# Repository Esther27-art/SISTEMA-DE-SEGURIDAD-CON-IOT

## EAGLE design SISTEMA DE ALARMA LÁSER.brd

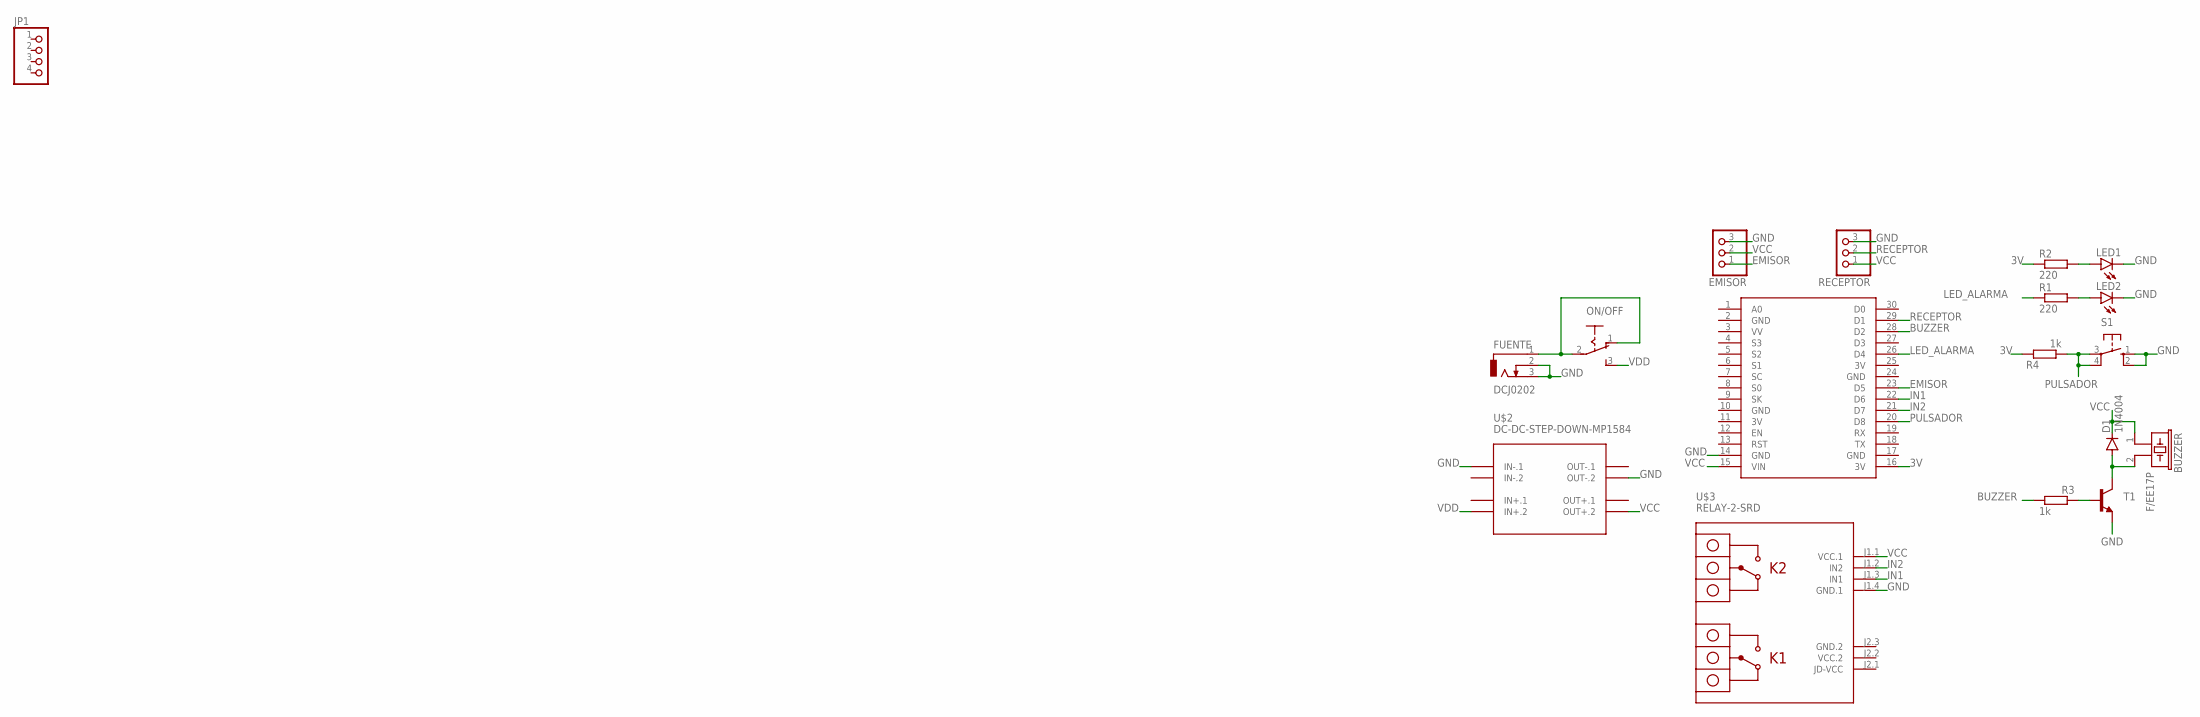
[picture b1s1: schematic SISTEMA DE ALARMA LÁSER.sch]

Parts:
BUZZER: F/EE17P
D1: 1N4004; DO41-10
EMISOR: PINHD-1X3; 1X03
FUENTE: DCJ0202
JP1: PINHD-1X4; 1X04
LED1, LED2: LED5MM
ON/OFF: 255SB
R1, R2: 220; 0204/7
R3, R4: 1k; 0204/7
RECEPTOR: PINHD-1X3; 1X03
S1: 10-XX; B3F-10XX
T1: 2N2222-NPN-TO92-EBC; TO92-EBC
U$1: NODEMCU
U$2: DC-DC-STEP-DOWN-MP1584
U$3: RELAY-2-SRD

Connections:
3V: R2.1, R4.2, U$1.11 (3V), U$1.16 (3V), U$1.25 (3V)
BUZZER: R3.1, U$1.28 (D2)
EMISOR: EMISOR.1, U$1.23 (D5)
GND: EMISOR.3, FUENTE.2, FUENTE.3, LED1.K (C), LED2.K (C), RECEPTOR.3, S1.1 (S), S1.2 (S1), T1.E, U$1.2 (GND), U$1.10 (GND), U$1.14 (GND), U$1.17 (GND), U$1.24 (GND), U$2.IN-.1, U$2.OUT-.2, U$3.J1.4 (GND.1)
GND.2: U$3.J2.3 (GND.2)
IN1: U$1.22 (D6), U$3.J1.3 (IN1)
IN2: U$1.21 (D7), U$3.J1.2 (IN2)
LED_ALARMA: R1.1, U$1.26 (D4)
unnamed: LED1.A, R2.2
unnamed: LED2.A, R1.2
unnamed: R3.2, T1.B
unnamed: BUZZER.2, D1.A, T1.C
unnamed: FUENTE.1, ON/OFF.1 (O), ON/OFF.2
PULSADOR: R4.1, S1.3, S1.4 (P1), U$1.20 (D8)
RECEPTOR: RECEPTOR.2, U$1.29 (D1)
VCC: BUZZER.1, D1.C, EMISOR.2, RECEPTOR.1, U$1.15 (VIN), U$2.OUT+.2, U$3.J1.1 (VCC.1)
VCC.2: U$3.J2.2 (VCC.2)
VDD: ON/OFF.3 (S), U$2.IN+.2

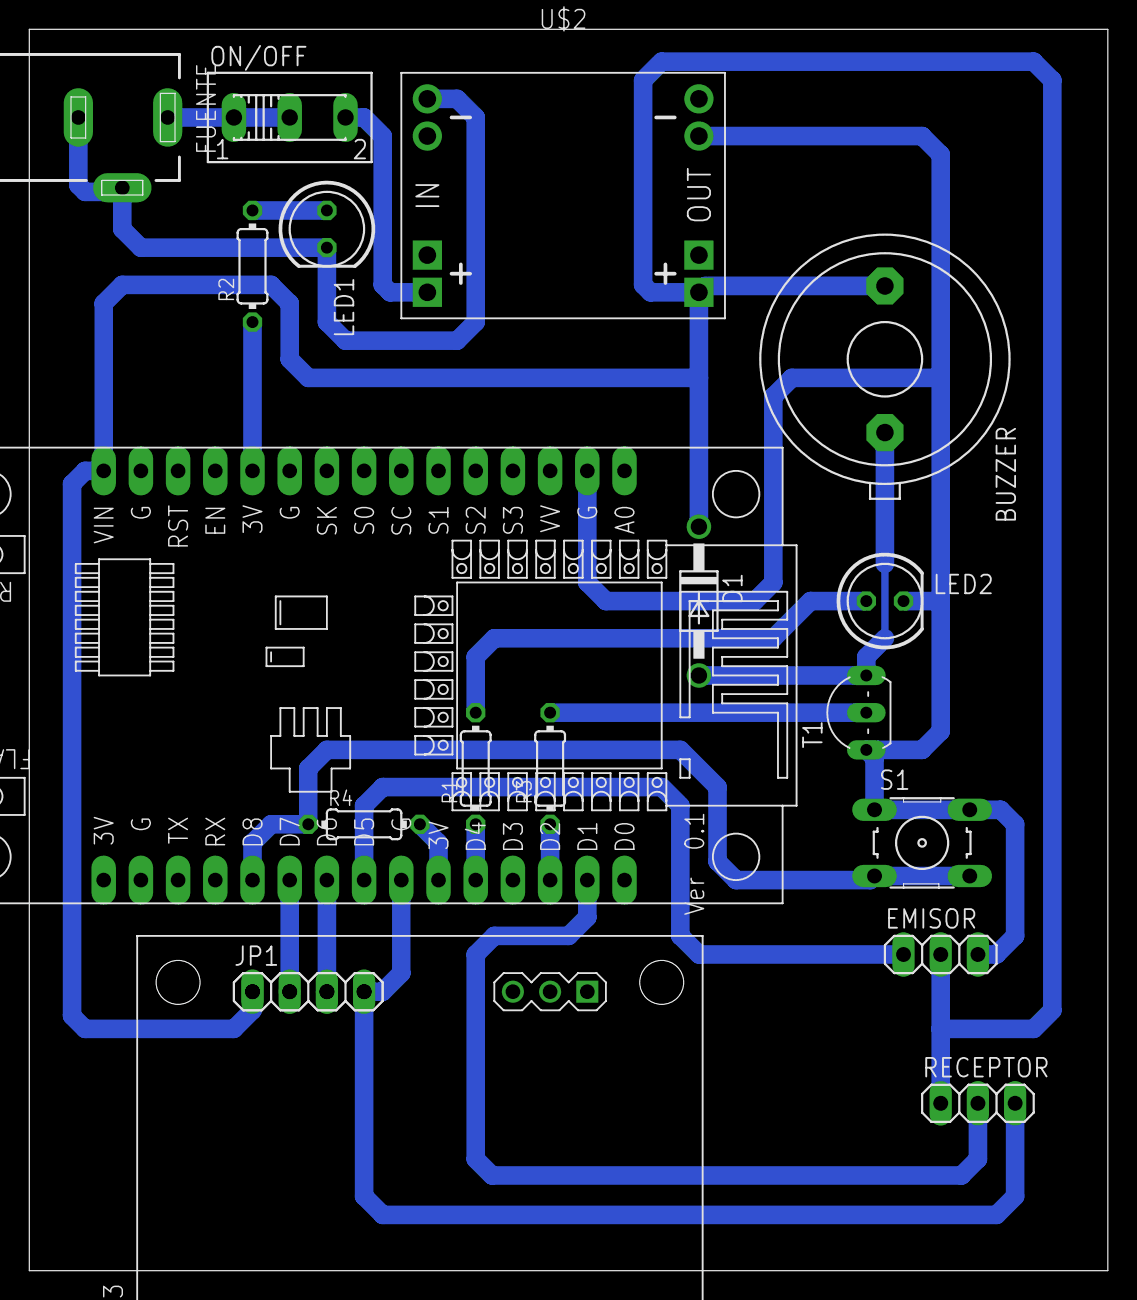
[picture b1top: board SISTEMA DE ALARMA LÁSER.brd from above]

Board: 2 copper layers, 73.6 x 84.8 mm, 18 parts (0 on the bottom side), 16 nets.

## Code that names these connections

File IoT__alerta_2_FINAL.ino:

#include "Arduino.h"
#include <EMailSender.h> //Libreria que permite enviar las alertas al correo electronico
#include <ESP8266WiFi.h> //Libreria que permite conectar el sistema a una red WiFi
#include <ThingerESP8266.h> //Libreria que permite vincular la NodeMCU con la plataforma IoT
//Parametros de conexion entre la placa NodeMCU y la plataforma Thinger.io
#define USERNAME "ISTEA" //Usuario
#define DEVICE_ID "NodeMCU" //Descripcion 
#define DEVICE_CREDENTIAL "qipFB8O@nAni66wd" //Credencial
#define boton_2 15//D8// Pin de señal de entrada del pulsador
#define botton A0// Pin de señal de entrada del encendido/apagado desde la IoT
const int receiverPin = 5; // D1/// Pin de señal de entrada del receptor / detector (el módulo usado solo devuelve un estado digital)    
const int buzzerPin =  4; // D2///  Pin de señal de salida del buzzer que indica cuando el sistema se dispara o detecta la presencia de intruso   
const int laserPin =  14; // D5/// Pin de señal de salida del módulo láser / puntero láser   
const int rele_1 =  12; // D6// Pin de señal de salida del rele_1
//const int rele_2 =  13; // D7// Pin de señal de salida del rele_2 para activar otra sirena o en caso de que se dañe la salida del rele 1  
ThingerESP8266 thing(USERNAME, DEVICE_ID, DEVICE_CREDENTIAL);
int receiverState = 0; 
int estado = 0;      
int contador = 0;
int alarma = 0;
int i;
int led_pulsador = 2; //D4/// // Pin de señal de salida del led que indica el encendido/apagado del sistema 
//const int LEDPin =  2;  //D4/// Pin de señal de salida del led que indica cuando el sistema se dispara o detecta la presencia de intruso   

bool cambio=false;
int pulsos_a = 0;
boolean anterior_a;
unsigned long tiempo1 = 0;
unsigned long tiempo2 = 0;

    uint8_t connection_state = 0;
    uint16_t reconnect_interval = 10000;
    EMailSender emailSend("isteaesmeraldas@gmail.com", "ISTEA2021");

uint8_t WiFiConnect(const char* nSSID = nullptr, const char* nPassword = nullptr)
{
    static uint16_t attempt = 0;
    Serial.print("Connecting to ");
    if(nSSID) {
        WiFi.begin(nSSID, nPassword);
        Serial.println(nSSID);
    }

    uint8_t i = 0;
    while(WiFi.status()!= WL_CONNECTED && i++ < 50)
    {
        delay(200);
        Serial.print(".");
    }
    ++attempt;
    Serial.println("");
    if(i == 51) {
        Serial.print("Connection: TIMEOUT on attempt: ");
        Serial.println(attempt);
        if(attempt % 2 == 0)
        Serial.println("Check if access point available or SSID and Password\r\n");
        return false;
    }
    Serial.println("Connection: ESTABLISHED");
    Serial.print("Got IP address: ");
    Serial.println(WiFi.localIP());
    return true;
}
void Awaits()
{
    uint32_t ts = millis();
    while(!connection_state)
    {
        delay(50);
        if(millis() > (ts + reconnect_interval) && !connection_state){
            connection_state = WiFiConnect();
            ts = millis();
        }
    }
}
void setup()
{
  Serial.begin(115200);
  pinMode(laserPin, OUTPUT); // Se establece el pin láser en modo de salida     
  //pinMode(LEDPin, OUTPUT);  // Se establece el pin LED en modo de salida    
  pinMode(buzzerPin, OUTPUT);  // Se establece el pin buzzer en modo de salida 
  pinMode(rele_1, OUTPUT); // Se establece el pin del rele_1 en modo de salida
  //pinMode(rele_2, OUTPUT); // Se establece el pin del rele_2 en modo de salida, en caso de averiarse el rele_1   
  pinMode(receiverPin, INPUT); // Se establece el pin receptor en modo de entrada, el módulo del receptor láser envía una señal ALTA cuando el láser lo ilumina. 
  pinMode(botton, INPUT); // Se establece el pin de encendido/apagado desde la IoT en modo de salida
  attachInterrupt(digitalPinToInterrupt(boton_2), boton, CHANGE);
  pinMode(led_pulsador,OUTPUT); // Se establece el pin de encendido/apagado del sistema en modo de salida 
  pinMode(boton_2, INPUT); // Se establece el pin del pulsador en modo de entrada
  anterior_a = digitalRead(boton_2);
  tiempo1 = millis();
  const char* ssid = "STHERSIT@"; //Nombre de la red a la que se va a conectar el dispositivo 
  const char* password = "Jhair1512@"; //Contraseña de la red
  connection_state = WiFiConnect(ssid, password);
  if(!connection_state)  // if not connected to WIFI
  Awaits();          // constantly trying to connec
  alarma=1;
  digitalWrite(laserPin, LOW); // Laser apagado 
  digitalWrite(buzzerPin, LOW); // Buzzer apagado
  //digitalWrite(rele_1, !HIGH); // Led apagado
  cambio=false;
  //thing.add_wifi(SSID, SSID_PASSWORD);
  //Codigos para enviar el estado del sistema desde la plataforma IoT Thinger.io
  thing["botton"] << digitalPin(botton);
  thing["led_pulsador"] << digitalPin(led_pulsador);
  thing["botton"]<< [](pson& activated){
    bool on = activated;
    if(activated){
      Serial.println("Sistema encendido remotamente");
      pulsos_a = 1;
      }
      else{
        pulsos_a = 2;
      }
      };
     }
void loop()
{   
  Serial.println(alarma);  
  if(pulsos_a==1){ 
    digitalWrite(laserPin, HIGH); //Laser encendido
    Serial.println("sistema encendido"); //Mensaje
    digitalWrite(led_pulsador, HIGH); //Led indicador enciende
    if (cambio==false){      
      receiverState = digitalRead(receiverPin);// leer el estado del valor de los receptores: 
      if (receiverState == HIGH) {    // si lo es, reciverState es HIGH: 
        digitalWrite(laserPin, HIGH); //Laser encendido 
        digitalWrite(rele_1, !HIGH); //Rele_1 apagado
        //digitalWrite(rele_2, LOW); //Rele_2 apagado
        digitalWrite(buzzerPin, LOW); //Buzzer apagado
        //digitalWrite(LEDPin, LOW); //Led apagado   
        Serial.println("alarma desactivada");  
      } 
      else { // Activa la alarma y sonara:
        thing.stop(); //
        digitalWrite(buzzerPin, HIGH);//Se enciende el buzzer
        //digitalWrite(LEDPin, HIGH); //Se enciende el led
        digitalWrite(rele_1, !LOW); //Se enciende el Rele_1 
        //digitalWrite(rele_2, HIGH); //Se enciende el Rele_2 
        digitalWrite(laserPin, HIGH);//El laser permanece encendido
        Serial.println("enviando mensaje");
        enviar_email();//Se envia el mensaje al correo electronico del administrador
        Serial.println("mensaje enviado"); 
        alarma=1; 
        thing.handle();
         tiempo2 = millis();
      if(tiempo2 > (tiempo1+1000)){  //Si ha pasado 1 segundo ejecuta el IF
          tiempo1 = millis(); //Actualiza el tiempo actual
       }
      }
    }
  } 
  // Activacion del sistema de alarma
  if (alarma == 1){
    cambio=true;
    digitalWrite(buzzerPin, HIGH);//Se enciende el buzzer
    //digitalWrite(LEDPin, HIGH); //Se enciende el led
    digitalWrite(rele_1, !LOW); //Se enciende el Rele_1 
        //digitalWrite(rele_2, HIGH); //Se enciende el Rele_2 
    digitalWrite(laserPin, HIGH);//El laser permanece encendido
   }
   // Desactivacion del sistema de alarma
  if (alarma == 0){
    cambio=false;
    //digitalWrite(laserPin, HIGH);//El laser permanece encendido
    digitalWrite(rele_1, !HIGH); //Se apaga el Rele_1 
    //digitalWrite(rele_2, LOW); //Se apaga el el Rele_2 
    digitalWrite(buzzerPin, LOW); //Se apaga el buzzer
    //digitalWrite(LEDPin, LOW); //Se apaga el led 
     }    
  if(pulsos_a>=2)
  {
    alarma=1;
    Serial.println("Sistema apagado");
    digitalWrite(led_pulsador, LOW);
    pulsos_a=0;
  }
  thing.handle(); //Subfuncion para la actualizacion de datos en la plataforma
}

ICACHE_RAM_ATTR void boton() {
  //delay(200);
 boolean estado_a = digitalRead(boton_2);
  if (anterior_a != estado_a) {
    if (estado_a == HIGH) {  //flanco descendente pull-up
      tiempo2 = millis();
      if(tiempo2 > (tiempo1+200)){  //Si ha pasado 1 segundo ejecuta el IF
          tiempo1 = millis(); //Actualiza el tiempo actual
          pulsos_a++;
          Serial.println(pulsos_a);
      }
    }
  }
}

void enviar_email(){
  //Codigo para el envio de alertas al correo electronico
    EMailSender::EMailMessage message;
    message.subject = "URGENTE ALARMA ACTIVADA"; //Mensaje
    message.message = "Alerta la seguridad del Instituto ha sido vulnerada"; //Mensaje para el usuario
    EMailSender::Response resp = emailSend.send("isteaesmeraldas@gmail.com",message); //Correo al que llegaran las alertas, puede ser reemplazado
    Serial.println("Sending status: ");
    Serial.println(resp.status);
    Serial.println(resp.code);
    Serial.println(resp.desc);
    
}

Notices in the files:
parts and their libraries:
diy-modules: Released under the Creative Commons Attribution 4.0 International License: http://creativecommons.org/licenses/by/4.0
